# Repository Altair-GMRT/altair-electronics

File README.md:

# **altair-electronics**

## **1. Contents**

- **altair-mcu/**

    This folder contains the Arduino IDE source code for the Altair MCU's firmware. Make sure the following libraries have been installed on your IDE before compiling:

    1. [**Adafruit GFX**](https://github.com/adafruit/Adafruit-GFX-Library)
    2. [**Adafruit SSD1306**](https://github.com/adafruit/Adafruit_SSD1306)
    3. [**Adafruit Sensor**](https://github.com/adafruit/Adafruit_Sensor)
    4. [**Adafruit BNO055**](https://github.com/adafruit/Adafruit_BNO055)

- **design/**

    This folder contains the Eagle/Fusion schematics and board designs, including the libraries used.

## **2. Electronics Design**
The robot will be powered by 4s 35c 5200mAh Li-Po battery. Hence, the battery voltage will be in the range of 12.8V - 16.8V with a maximum discharge of 182A. The Raspberry Pi 5 needs 5V 5A power supply, and 20 Dynamixel MXs need 14V 2A per servo. We will convert the battery voltage to supply those two with a 5V regulator and a Buck-Boost Converter, respectively. Read more about the design at ```design/simulations```.

### **2.1 Buck-Boost Converter**
The buck and the boost in the Buck-Boost Converter will be used interchangeably. The equation describing the behaviour of the buck is:

$$V_{out} = DV_{in}$$

$$I_{ripple} = V_{out}\left(\frac{1}{R} \pm \frac{1 - D}{2L}T \right)$$

$$V_{ripple} \propto \frac{(1-D)V_{out}T^2}{8LC}$$

and for the boost:

$$V_{out} = \frac{1}{1 - D}V_{in}$$

$$I_{ripple} = V_{in}\left(\frac{1}{R(1-D)^2} \pm \frac{1}{2L}DT\right)$$

$$V_{ripple} \propto \frac{DTV_{out}}{RC}$$

Consider the following table: 

|No.|Parameter|Value|
|:---:|:---:|:---:|
|1|$D_{buck}$|$[0.83, 1]$|
|2|$D_{boost}$|$[0, 0.086]$|
|3|$V_{in}$|$[12.8, 16.8]\text{V}$|
|4|$V_{out}$|$14\text{V}$|
|5|$I_{max}$|$30\text{A}$|
|6|$T_S$|$12.5\mu\text{s}$|
|7|$f_S$|$80\text{kHz}$|
|8|$R$|$V_{out}/I_{max} = 0.5\Omega$|

We obtain the optimal (smallest possible, yet acceptable performance) value of $L = 330\mu\text{H}$ and $C = 4.7\text{mF}$ in 3 parallels.

### **2.2 Components**
The following table shows the entire components required for assembling a complete circuit.

| No. | Component Name | Qty. | Datasheets |
| :---: | :--- | :---: | :---: |
| 1 | **ESP32-WROOM-32D** | | |
| 2 | **BNO055** 9-Axis IMU | | |
| 3 | **SSD1306** OLED Display | | |
| 4 | **LM2596S-5.0** 5V 3A Regulator | | |
| 5 | **1N5824** Schottky Diode | | |
| 6 | **CDRH127R** Power Inductor | | |
| 7 | **IRF9540** P-Channel Power MOSFET | | |
| 8 | **S9013** NPN Transistor | | |
| 9 | **SR5100 & 1N58219** Schottky Diode | | |
| 10 | **MOLEX 22-03-5035** Dynamixel Connector | | |
| 11 | **USB Female Type-C** | | |
| 12 | **USB Female Type-A** | | |
| 13 | **SMD Button** | | |

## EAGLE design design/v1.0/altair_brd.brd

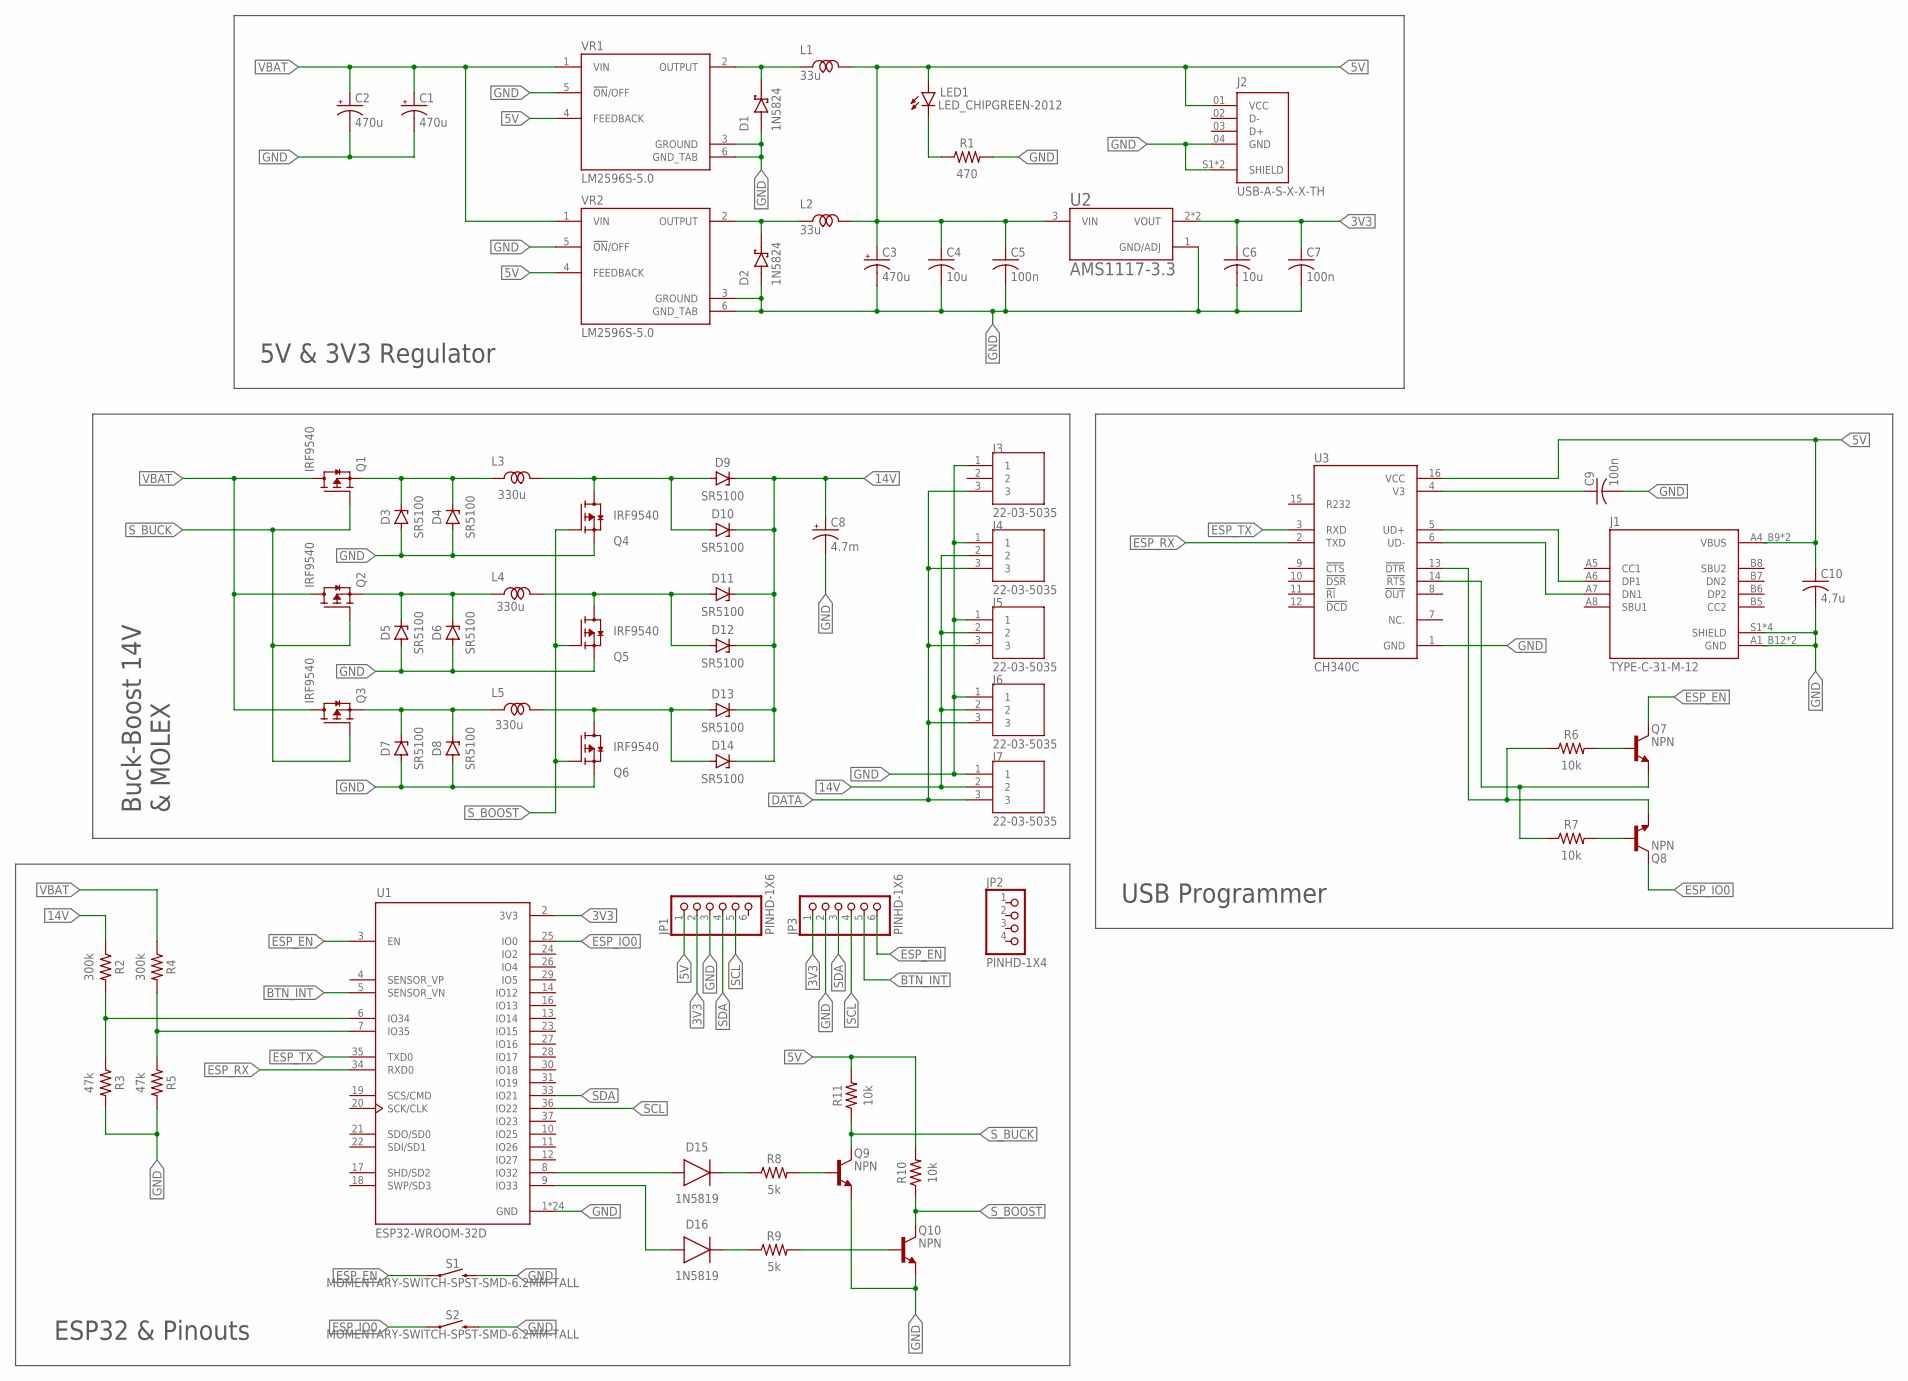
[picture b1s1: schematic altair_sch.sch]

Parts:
C1, C2, C3: 470u; CAPAE1030X1050N
C4, C6: 10u; CAPC2012X110
C5, C7, C9: 100n; CAPC2012X110
C8: 4.7m; CAPPRD550W60D1200H2000B
C10: 4.7u; CAPC2012X110
D1, D2: 1N5824; SODFL4725X110N
D3, D4, D5, D6, D7, D8, D9, D10, D11, D12, D13, D14: SR5100; DIOM5226X290N
D15, D16: 1N5819; DIOM5226X290N
J1: TYPE-C-31-M-12; HRO_TYPE-C-31-M-12
J2: USB-A-S-X-X-TH; SAMTEC_USB-A-S-X-X-TH
J3, J4, J5, J6, J7: 22-03-5035; MOLEX_22-03-5035
JP1, JP3: PINHD-1X6; 1X06
JP2: PINHD-1X4; 1X04
L1, L2: 33u; CDRH127R
L3, L4, L5: 330u; CDRH127R
LED1: LED_CHIPGREEN-2012; LEDC2012X110N_G
Q1, Q2, Q3, Q4, Q5, Q6: IRF9540; TO254P1052X465X1989-3
Q7, Q8, Q9, Q10: NPN; SOT95P237X112-3N
R1: 470; RESC2012X65
R2, R4: 300k; RESC2012X65
R3, R5: 47k; RESC2012X65
R6, R7, R10, R11: 10k; RESC2012X65
R8, R9: 5k; RESC2012X65
S1, S2: MOMENTARY-SWITCH-SPST-SMD-6.2MM-TALL; TACTILE_SWITCH_SMD_6.2MM_TALL
U1: ESP32-WROOM-32D; MODULE_ESP32-WROOM-32D
U2: AMS1117-3.3; SOT229P700X180-4N
U3: CH340C; SOIC127P600X180-16N
VR1, VR2: LM2596S-5.0; TO170P1524X483-6N

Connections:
3V3: C6.1, C7.1, JP1.2, JP3.1, U1.2 (3V3), U2.2 (VOUT), U2.4 (VOUT)
5V: C3.1 (+), C4.1, C5.1, C10.1, J1.A4_B9 (VBUS), J1.B4_A9 (VBUS), J2.01 (VCC), JP1.1, L1.P$2, L2.P$2, LED1.2 (A), R10.2, R11.2, U2.3 (VIN), U3.16 (VCC), VR1.4 (FEEDBACK), VR2.4 (FEEDBACK)
14V: C8.1 (+), D9.1 (C), D10.1 (C), D11.1 (C), D12.1 (C), D13.1 (C), D14.1 (C), J4.2, J5.2, J6.2, J7.2, R2.1
BTN_INT: JP3.5, U1.5 (SENSOR_VN)
DATA: J3.3, J4.3, J5.3, J6.3, J7.3
ESP_EN: JP3.6, Q7.3 (C), S1.A2 (1), U1.3 (EN)
ESP_IO0: Q8.3 (C), S2.A2 (1), U1.25 (IO0)
ESP_RX: U1.34 (RXD0), U3.2 (TXD)
ESP_TX: U1.35 (TXD0), U3.3 (RXD)
GND: C1.2 (-), C2.2 (-), C3.2 (-), C4.2, C5.2, C6.2, C7.2, C8.2 (-), C9.2, C10.2, D1.A, D2.A, D3.2 (A), D4.2 (A), D5.2 (A), D6.2 (A), D7.2 (A), D8.2 (A), J1.A1_B12 (GND), J1.B1_A12 (GND), J1.S1 (SHIELD), J1.S2 (SHIELD), J1.S3 (SHIELD), J1.S4 (SHIELD), J2.04 (GND), J2.S1 (SHIELD), J2.S2 (SHIELD), J3.1, J4.1, J5.1, J6.1, J7.1, JP1.3, JP3.2, Q4.3 (S), Q5.3 (S), Q6.3 (S), Q9.2 (E), Q10.2 (E), R1.2, R3.2, R5.2, S1.B2 (2), S2.B2 (2), U1.1 (GND), U1.15 (GND), U1.38 (GND), U1.39_1 (GND), U1.39_2 (GND), U1.39_3 (GND), U1.39_4 (GND), U1.39_5 (GND), U1.39_6 (GND), U1.39_7 (GND), U1.39_8 (GND), U1.39_9 (GND), U1.39_10 (GND), U1.39_11 (GND), U1.39_12 (GND), U1.39_13 (GND), U1.39_14 (GND), U1.39_15 (GND), U1.39_16 (GND), U1.39_17 (GND), U1.39_18 (GND), U1.39_19 (GND), U1.39_20 (GND), U1.39_21 (GND), U2.1 (GND/ADJ), U3.1 (GND), VR1.3 (GROUND), VR1.5 (!ON!/OFF), VR1.6 (GND_TAB), VR2.3 (GROUND), VR2.5 (!ON!/OFF), VR2.6 (GND_TAB)
unnamed: D1.C (K), L1.P$1, VR1.2 (OUTPUT)
unnamed: LED1.1 (C), R1.1
unnamed: D3.1 (C), D4.1 (C), L3.P$1, Q1.3 (S)
unnamed: D2.C (K), L2.P$1, VR2.2 (OUTPUT)
unnamed: D5.1 (C), D6.1 (C), L4.P$1, Q2.3 (S)
unnamed: D7.1 (C), D8.1 (C), L5.P$1, Q3.3 (S)
unnamed: D9.2 (A), D10.2 (A), L3.P$2, Q4.2 (D)
unnamed: D11.2 (A), D12.2 (A), L4.P$2, Q5.2 (D)
unnamed: D13.2 (A), D14.2 (A), L5.P$2, Q6.2 (D)
unnamed: R4.2, R5.1, U1.7 (IO35)
unnamed: R2.2, R3.1, U1.6 (IO34)
unnamed: C9.1, U3.4 (V3)
unnamed: J1.A6 (DP1), U3.5 (UD+)
unnamed: J1.A7 (DN1), U3.6 (UD-)
unnamed: Q7.2 (E), R7.1, U3.14 (!RTS)
unnamed: Q8.2 (E), R6.1, U3.13 (!DTR)
unnamed: Q7.1 (B), R6.2
unnamed: Q8.1 (B), R7.2
unnamed: D15.2 (A), U1.8 (IO32)
unnamed: D15.1 (C), R8.1
unnamed: D16.2 (A), U1.9 (IO33)
unnamed: D16.1 (C), R9.1
unnamed: Q10.1 (B), R9.2
unnamed: Q9.1 (B), R8.2
SCL: JP1.5, JP3.4, U1.36 (IO22)
SDA: JP1.4, JP3.3, U1.33 (IO21)
S_BOOST: Q4.1 (G), Q5.1 (G), Q6.1 (G), Q10.3 (C), R10.1
S_BUCK: Q1.1 (G), Q2.1 (G), Q3.1 (G), Q9.3 (C), R11.1
VBAT: C1.1 (+), C2.1 (+), Q1.2 (D), Q2.2 (D), Q3.2 (D), R4.1, VR1.1 (VIN), VR2.1 (VIN)

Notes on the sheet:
5V & 3V3 Regulator
Buck-Boost 14V & MOLEX
USB Programmer
ESP32 & Pinouts

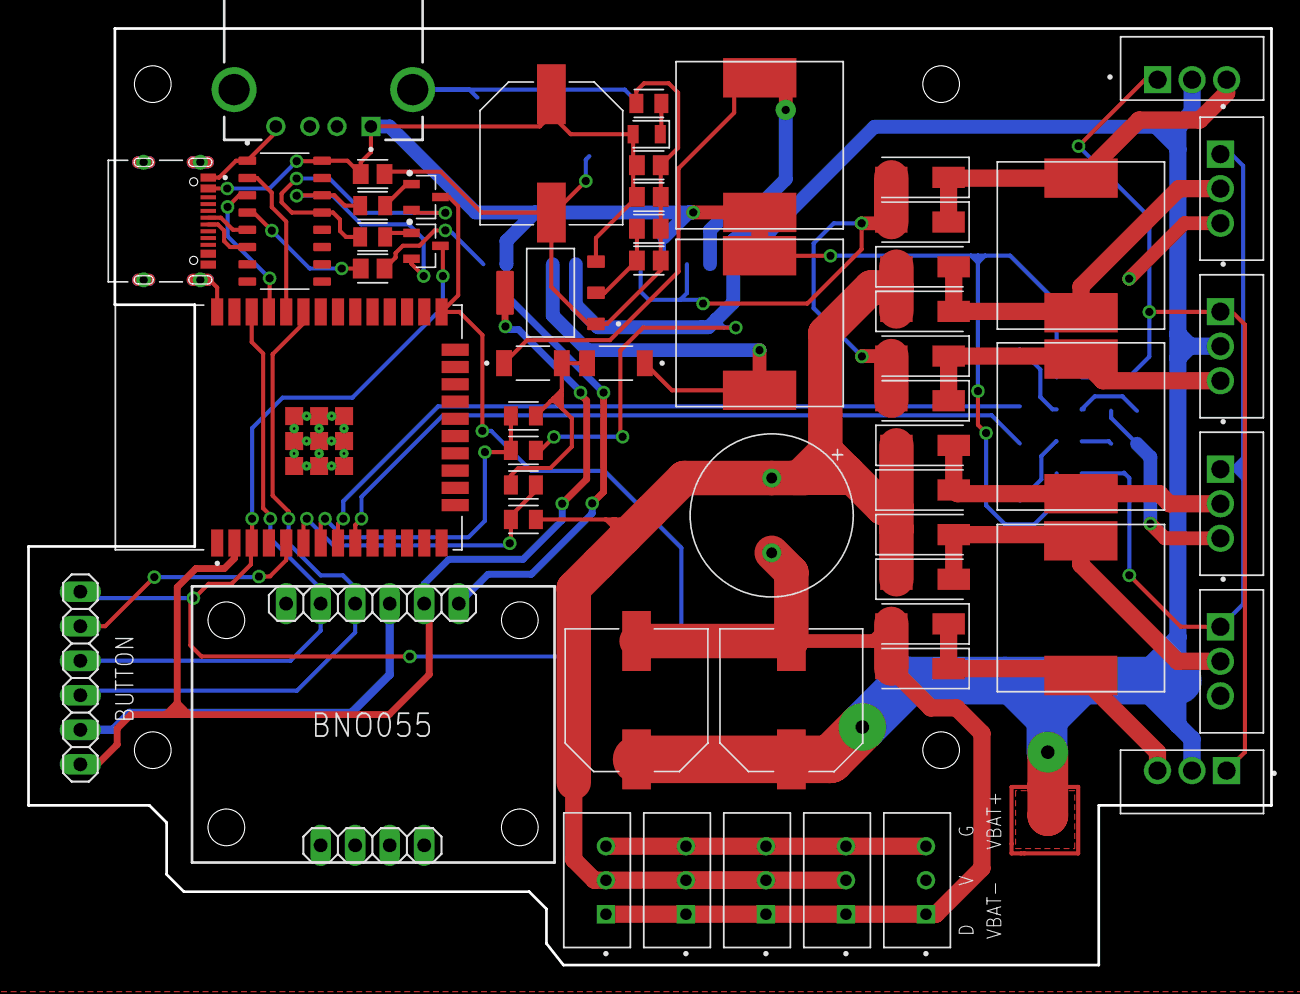
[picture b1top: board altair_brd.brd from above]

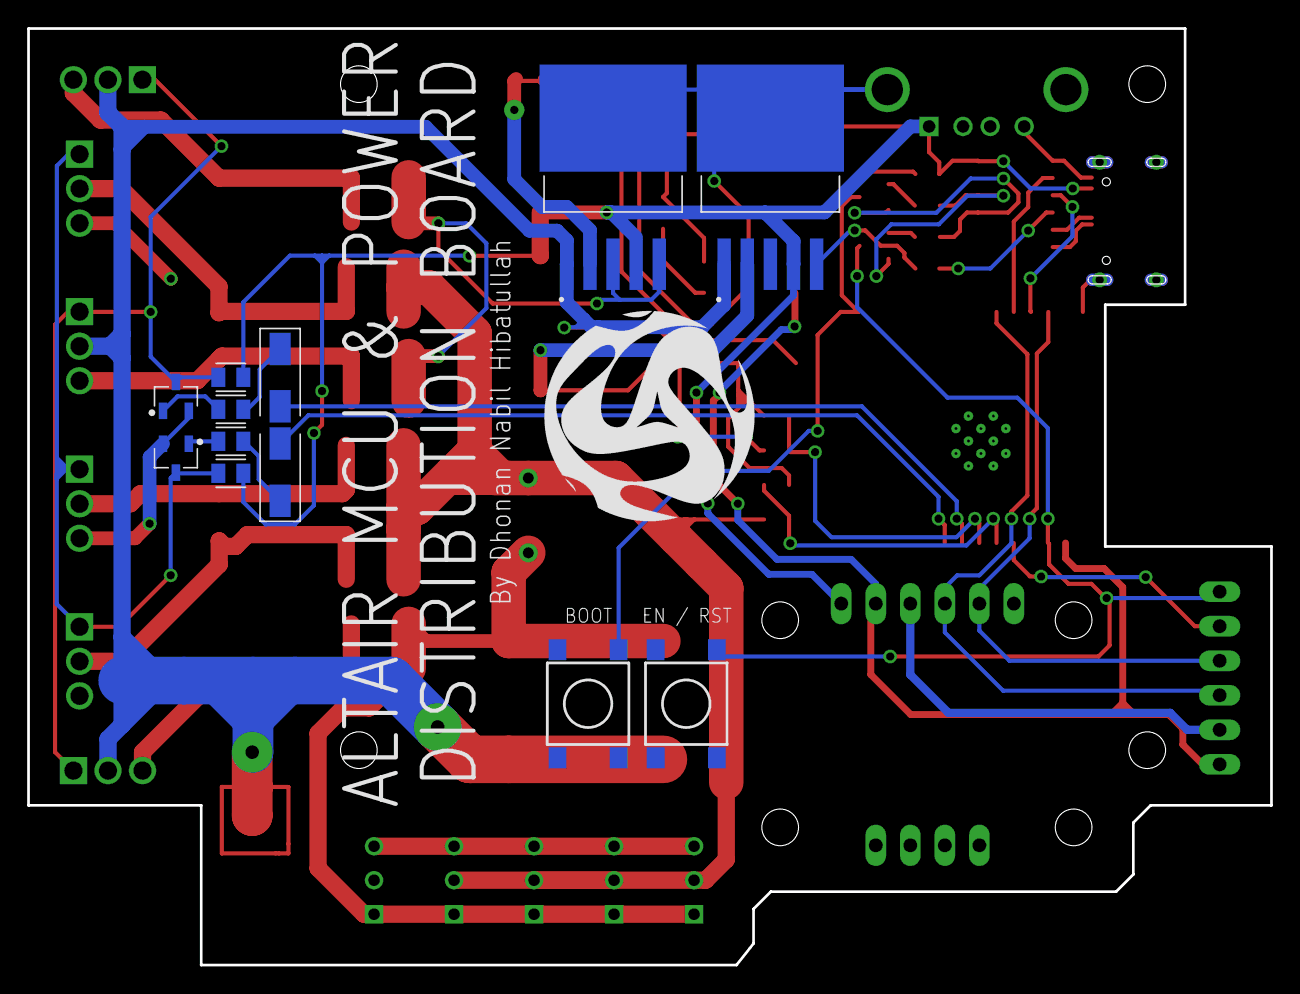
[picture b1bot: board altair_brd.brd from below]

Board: 2 copper layers, 91.4 x 68.9 mm, 70 parts (12 on the bottom side), 39 nets.

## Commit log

2024-04-01 Fix: directory restructured
2024-04-01 Chore: README added
2024-04-01 Fix: structure canceled
2024-04-01 Feat: ESP32 lbr and STEP added
2024-04-01 Chore: README fixed.
2024-04-16 First version added
2024-04-16 README updated
2024-04-19 File type changed (9.x compatible)
2024-04-20 Version fixed
2024-04-20 Images updated
2024-04-20 Button interrupt added

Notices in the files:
parts and their libraries:
SparkFun-Switches: Licensing: Creative Commons ShareAlike 4.0 International - https://creativecommons.org/licenses/by-sa/4.0
